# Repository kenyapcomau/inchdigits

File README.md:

# 1 inch tall 4 digit 7 segment display driven by TM1637

These are the Kicad design files for my Hackaday project [Inch Digits](https://hackaday.io/project/169179-inch-digits)

## Versioning

February 2020

## Notes

## Authors

* **Ken Yap**

## License

See the [LICENSE](LICENSE.md) file for license rights and limitations (MIT).

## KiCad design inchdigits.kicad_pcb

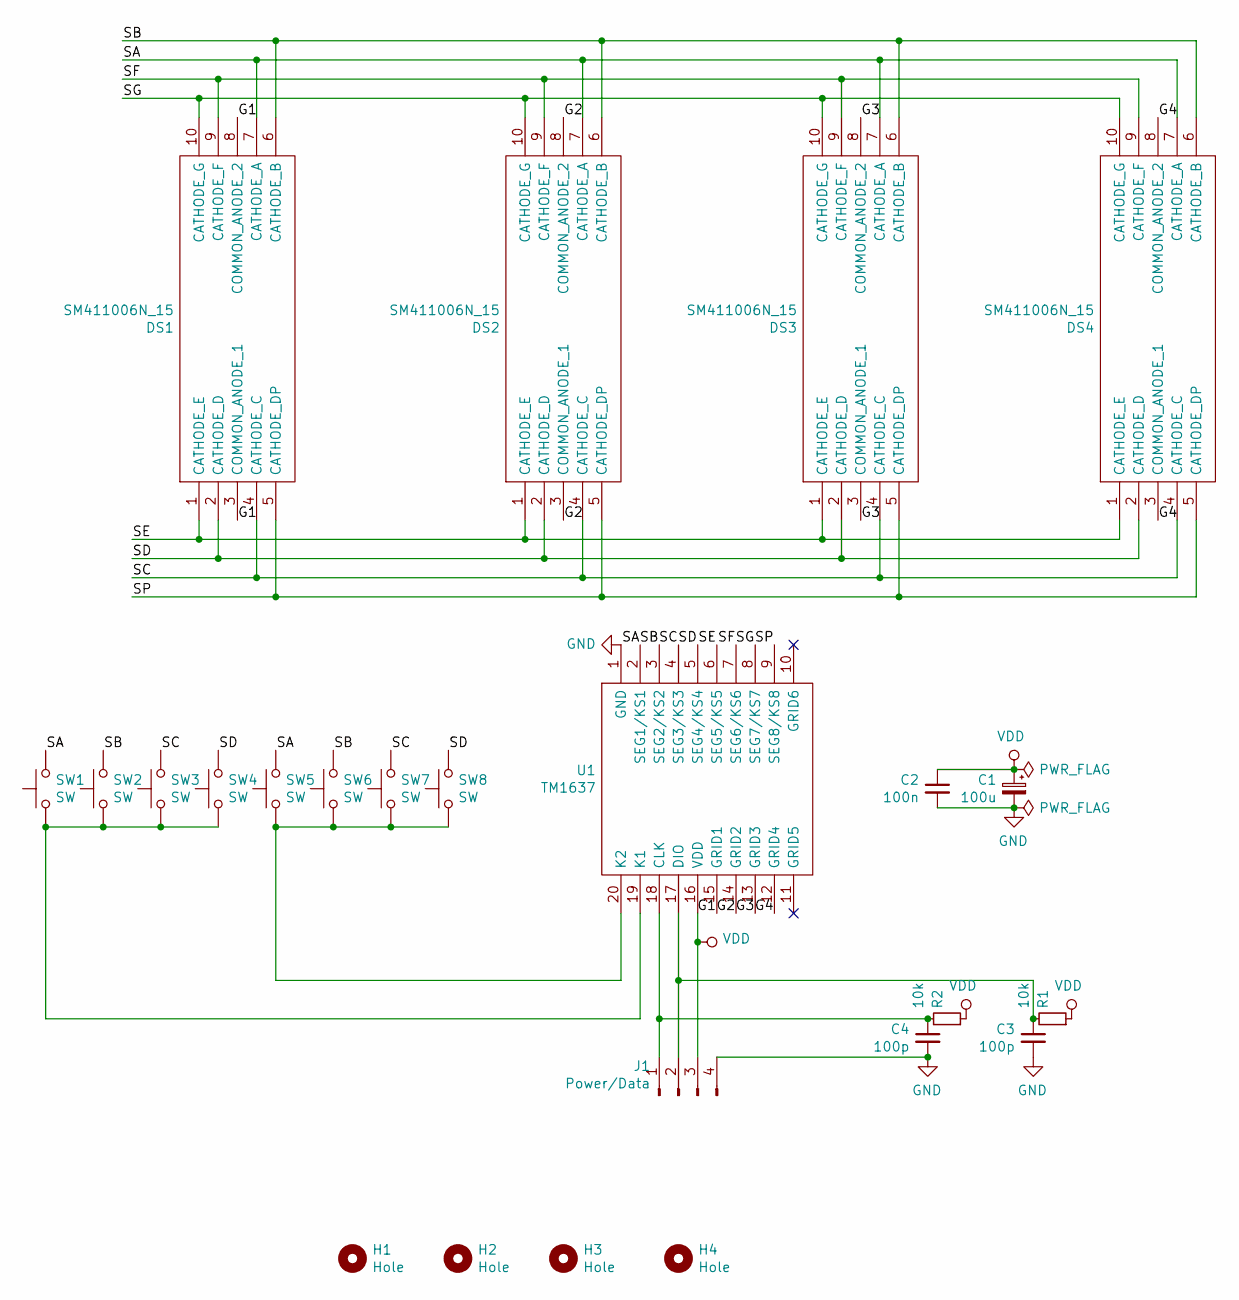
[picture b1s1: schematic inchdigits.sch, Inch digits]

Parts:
C1: 100u; C_Radial_D8.0mm_H11.5mm_P3.50mm
C2: 100n; C_Rect_L7.0mm_W2.5mm_P5.00mm
C3, C4: 100p; C_0805_2012Metric_Pad1.15x1.40mm_HandSolder
DS1, DS2, DS3, DS4: SM411006N_15; DIPS3048W51P254L2400H1075Q10N; Manufacturer_Part_Number SM411006N/15
H1, H2, H3, H4: Hole; MountingHole_3.5mm_Pad
J1: Power/Data; PinHeader_1x04_P2.54mm_Horizontal
R1, R2: 10k; R_0805_2012Metric_Pad1.15x1.40mm_HandSolder
SW1, SW2, SW3, SW4, SW5, SW6, SW7, SW8: SW; SW_PUSH_6mm_H5mm
U1: TM1637; SO-20_12.8x7.5mm_P1.27mm; Manufacturer_Part_Number TM1637

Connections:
/G1: DS1.3 (COMMON_ANODE_1), DS1.8 (COMMON_ANODE_2), U1.15 (GRID1)
/G2: DS2.3 (COMMON_ANODE_1), DS2.8 (COMMON_ANODE_2), U1.14 (GRID2)
/G3: DS3.3 (COMMON_ANODE_1), DS3.8 (COMMON_ANODE_2), U1.13 (GRID3)
/G4: DS4.3 (COMMON_ANODE_1), DS4.8 (COMMON_ANODE_2), U1.12 (GRID4)
/SA: DS1.7 (CATHODE_A), DS2.7 (CATHODE_A), DS3.7 (CATHODE_A), DS4.7 (CATHODE_A), SW1.2, SW5.2, U1.2 (SEG1/KS1)
/SB: DS1.6 (CATHODE_B), DS2.6 (CATHODE_B), DS3.6 (CATHODE_B), DS4.6 (CATHODE_B), SW2.2, SW6.2, U1.3 (SEG2/KS2)
/SC: DS1.4 (CATHODE_C), DS2.4 (CATHODE_C), DS3.4 (CATHODE_C), DS4.4 (CATHODE_C), SW3.2, SW7.2, U1.4 (SEG3/KS3)
/SD: DS1.2 (CATHODE_D), DS2.2 (CATHODE_D), DS3.2 (CATHODE_D), DS4.2 (CATHODE_D), SW4.2, SW8.2, U1.5 (SEG4/KS4)
/SE: DS1.1 (CATHODE_E), DS2.1 (CATHODE_E), DS3.1 (CATHODE_E), DS4.1 (CATHODE_E), U1.6 (SEG5/KS5)
/SF: DS1.9 (CATHODE_F), DS2.9 (CATHODE_F), DS3.9 (CATHODE_F), DS4.9 (CATHODE_F), U1.7 (SEG6/KS6)
/SG: DS1.10 (CATHODE_G), DS2.10 (CATHODE_G), DS3.10 (CATHODE_G), DS4.10 (CATHODE_G), U1.8 (SEG7/KS7)
/SP: DS1.5 (CATHODE_DP), DS2.5 (CATHODE_DP), DS3.5 (CATHODE_DP), DS4.5 (CATHODE_DP), U1.9 (SEG8/KS8)
GND: C1.2, C2.2, C3.2, C4.2, J1.4, U1.1 (GND)
unnamed: C3.1, J1.2, R1.2, U1.17 (DIO)
unnamed: C4.1, J1.1, R2.2, U1.18 (CLK)
unnamed: SW1.1, SW2.1, SW3.1, SW4.1, U1.19 (K1)
unnamed: SW5.1, SW6.1, SW7.1, SW8.1, U1.20 (K2)
VDD: C1.1, C2.1, J1.3, R1.1, R2.1, U1.16 (VDD)

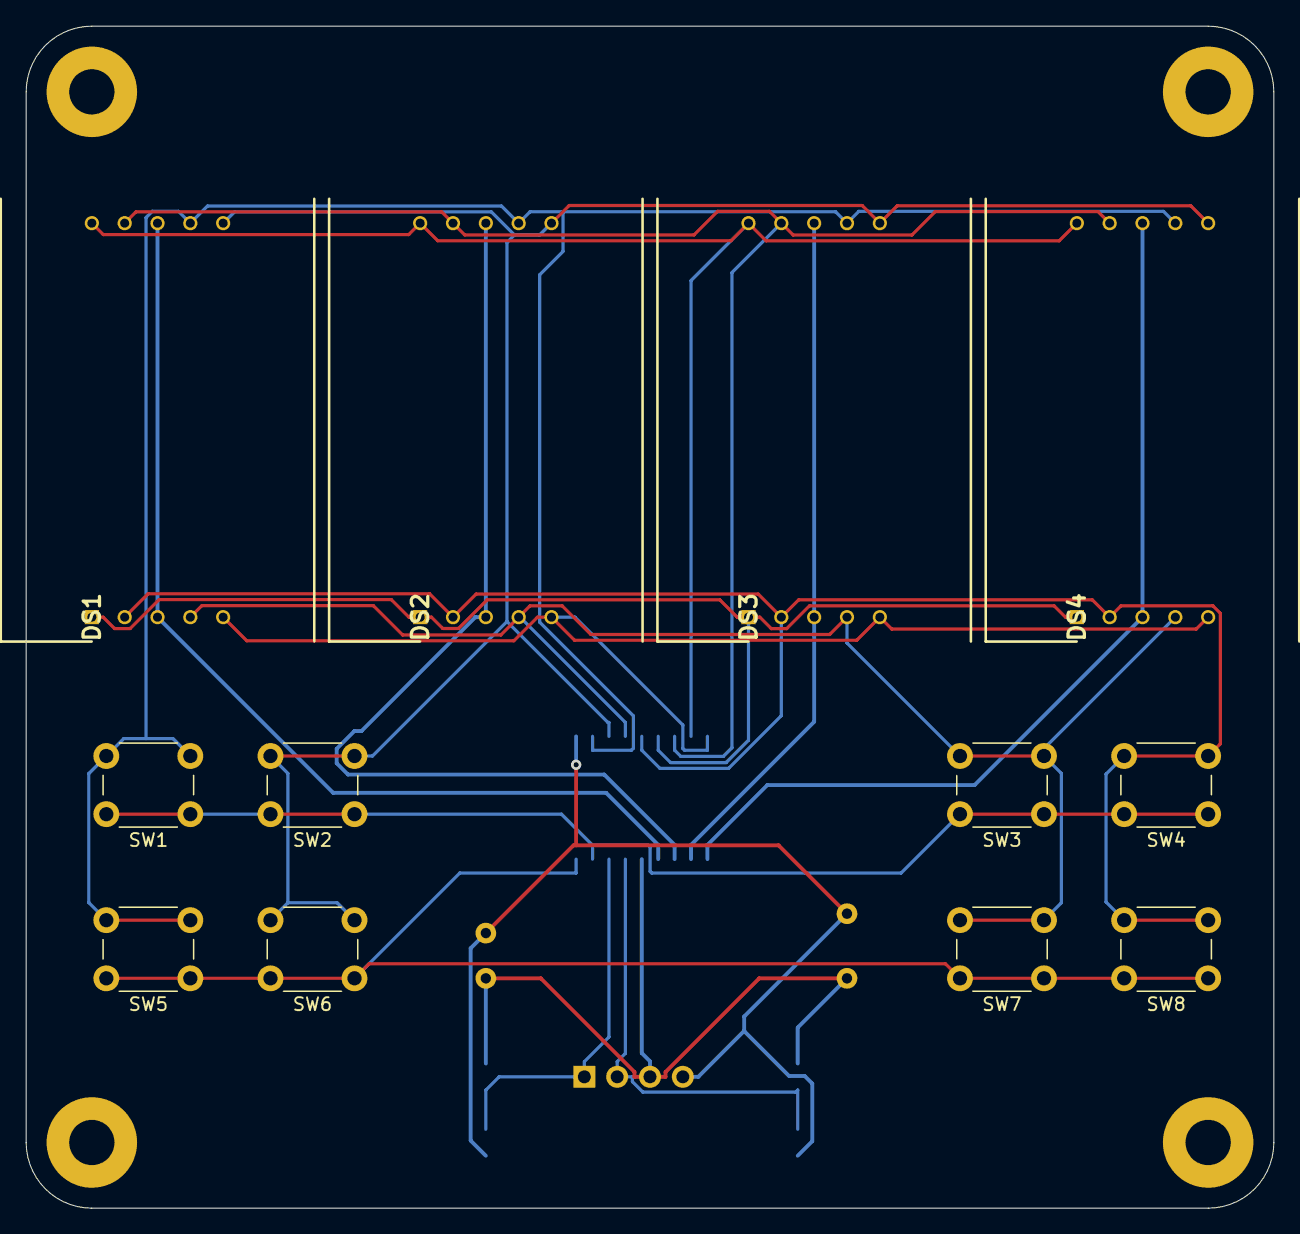
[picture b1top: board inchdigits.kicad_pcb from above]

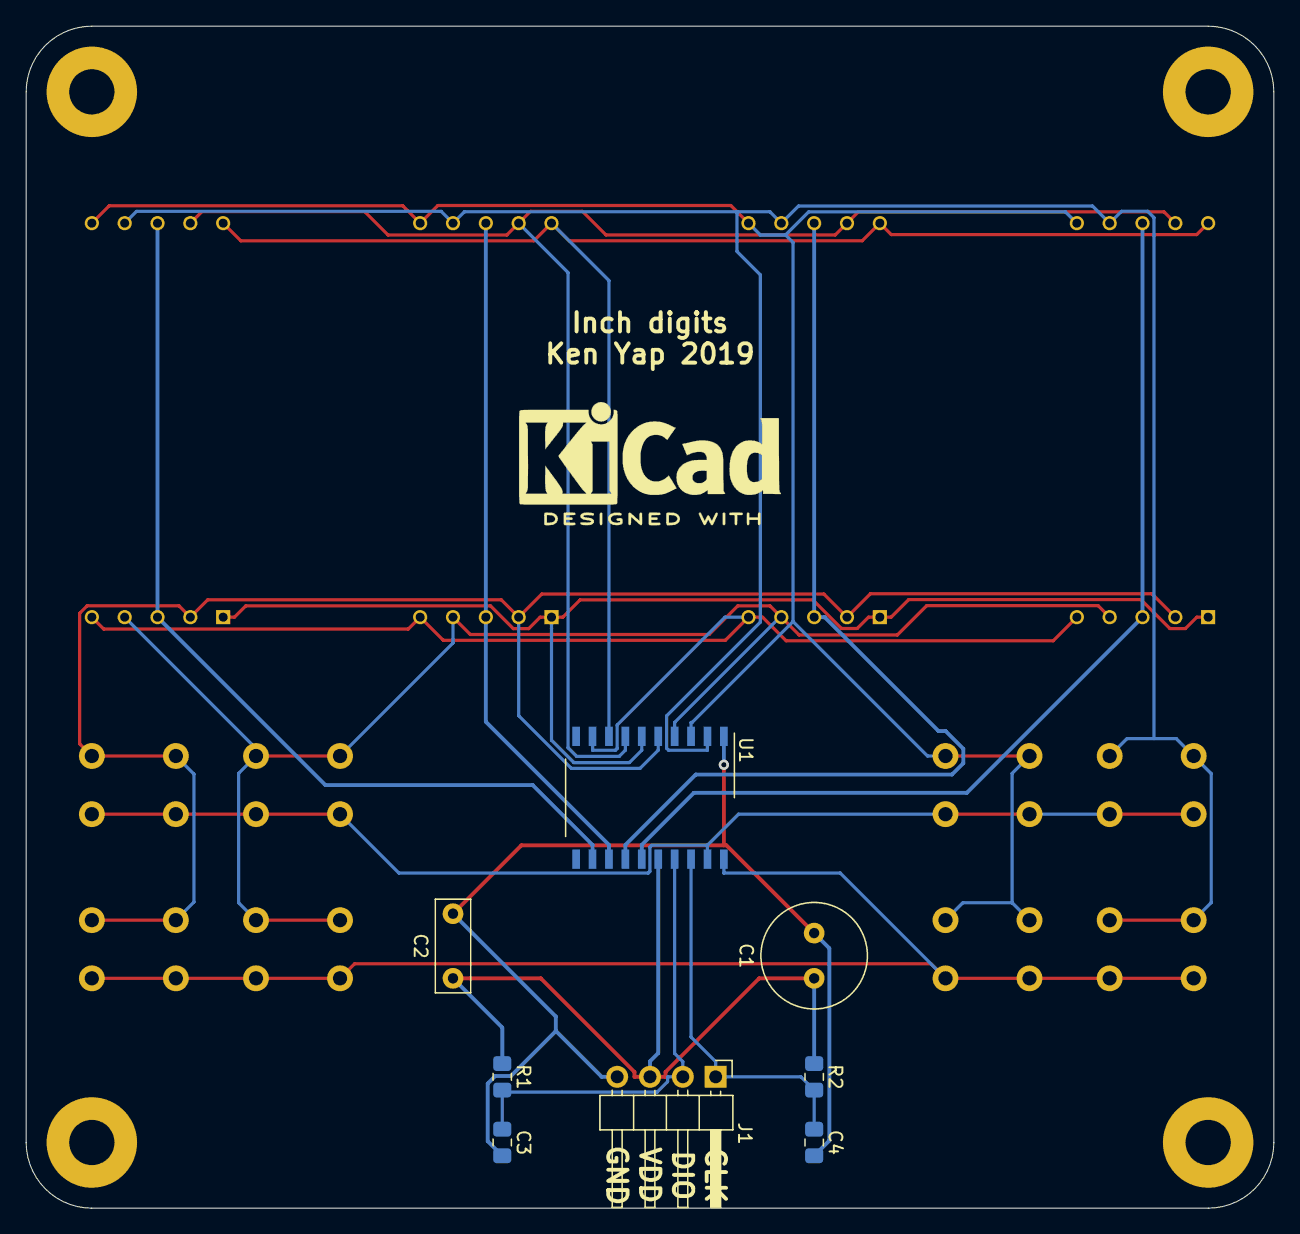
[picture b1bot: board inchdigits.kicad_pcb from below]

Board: 2 copper layers, 96.5 x 91.4 mm, 24 parts (8 on the bottom side), 18 nets.

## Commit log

2020-02-11 Initial release
2020-02-17 Figured how to "light up" segments
